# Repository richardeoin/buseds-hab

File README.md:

TODO: Find a better name for this project than "buseds-hab"!

### [Components List](Components.md)

### [Block Diagram](Block-Diagram.md)

### [Power Budget](power-budget.md)

### Design Notes

The electronics collects data from the sensors and GPS. [Common GPS errors](http://ukhas.org.uk/guides:common_coding_errors_payload_testing).

The data is formatted as a
[UKHAS Telemetry String](http://ukhas.org.uk/communication:protocol)
and transmitted on 434.075MHz using a NTX2
transmitter. [Useful guide to using NTX2](http://ukhas.org.uk/guides:linkingarduinotontx2).
The Telemetry Strings are also logged to a µSD card.

Gets received by Yaesu FT790R.

Audio links to laptop, UKHAS's
[dl-fldigi](http://ukhas.org.uk/projects:dl-fldigi) is used to decode and upload.

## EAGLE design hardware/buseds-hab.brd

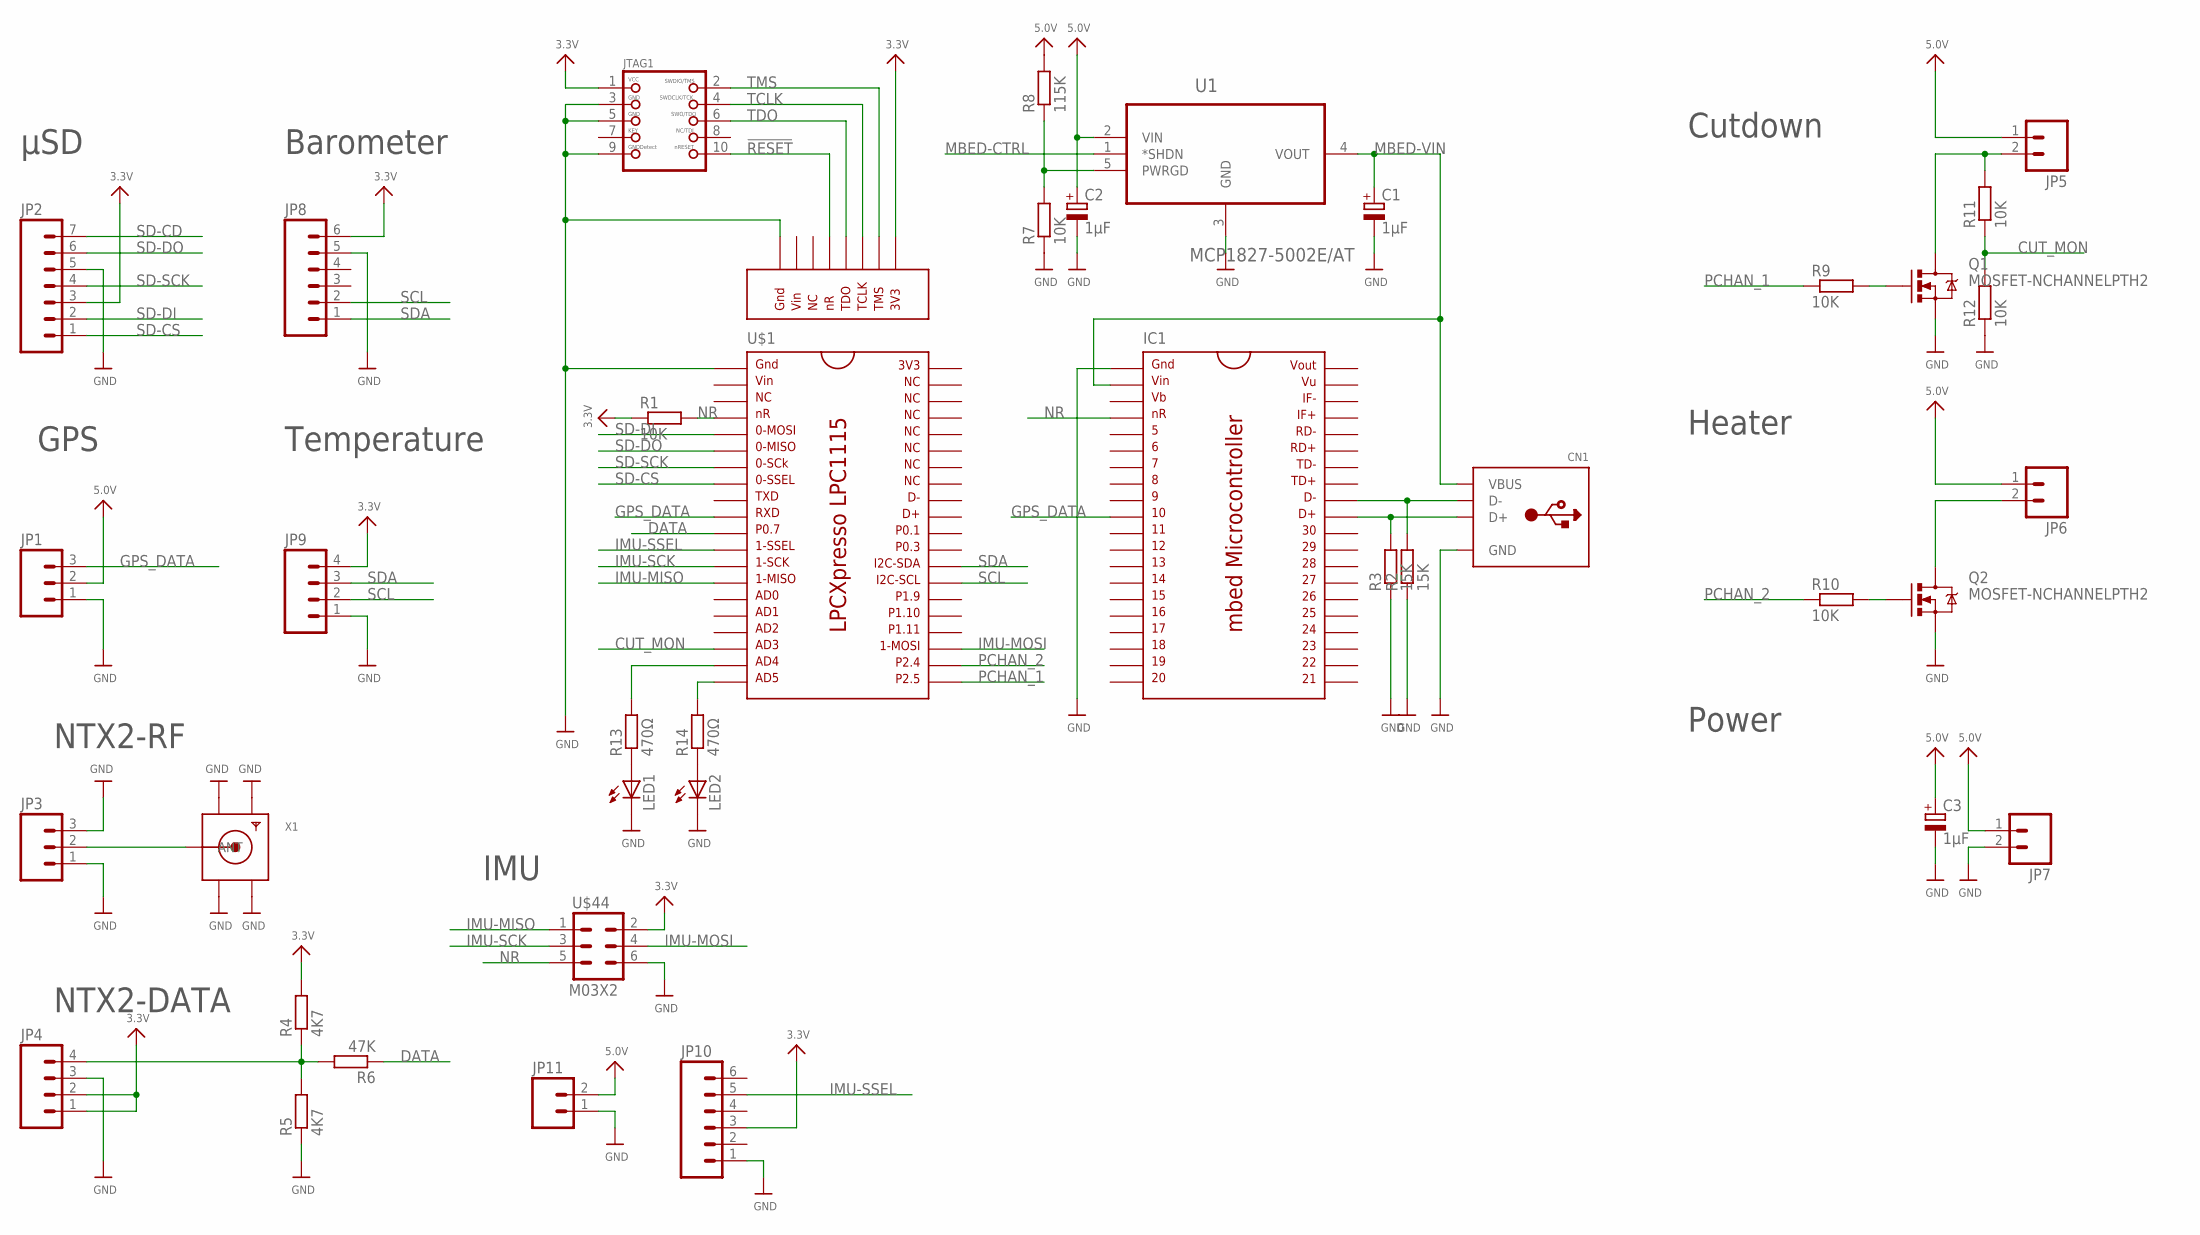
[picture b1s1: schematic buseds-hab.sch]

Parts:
C1, C2, C3: 1µF; E2-5
CN1: USB_TYPEAPTHFML; USB_HOST-PTH
IC1: MBED; DIL40_0.9
JP1, JP3: M03LOCK; 1X03_LOCK
JP2: M07LOCK; 1X07_LOCK
JP4, JP9: M04LOCK; 1X04_LOCK
JP5, JP6, JP7: M023.5MM_LOCK; SCREWTERMINAL-3.5MM-2_LOCK
JP8, JP10: M06LOCK; 1X06_LOCK
JP11: M02LOCK; 1X02_LOCK
JTAG1: JTAG-CORTEXM3; 2X05_1.27MM
LED1, LED2: LED3MM
Q1, Q2: MOSFET-NCHANNELPTH2; TO220V
R1, R7, R9, R10, R11, R12: 10K; 0204/7
R2, R3: 15K; 0204/7
R4, R5: 4K7; 0204/7
R6: 47K; 0204/7
R8: 115K; 0204/7
R13, R14: 470Ω; 0204/7
U1: MCP1827-5002E/AT; TO170P482X1024X3124-5P
U$1: LPCXPRESSOLPC; LPCXPRESSO
U$44: M03X2; 2X3_LOCK
X1: SMACONNECTOR; SMA90_DIP

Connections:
3.3V: JP2.3, JP4.1, JP4.2, JP8.6, JP9.4, JP10.3, JTAG1.1, R1.1, R4.2, U$1.P-1, U$44.2
5.0V: C2.+, C3.+, JP1.2, JP5.1, JP6.1, JP7.1, JP11.2, R8.2, U1.2 (VIN)
!RESET!: JTAG1.10, U$1.P-5
CUT_MON: R11.1, R12.2, U$1.18
D+: CN1.D+, IC1.31, R3.2
D-: CN1.D-, IC1.32, R2.2
DATA: R6.1, U$1.11
GND: C1.-, C2.-, C3.-, CN1.GND, IC1.1, JP1.1, JP2.5, JP3.1, JP3.3, JP4.3, JP7.2, JP8.5, JP9.1, JP10.1, JP11.1, JTAG1.3, JTAG1.5, JTAG1.9, LED1.K (C), LED2.K (C), Q1.3 (S), Q2.3 (S), R2.1, R3.1, R5.1, R7.1, R12.1, U1.3 (GND), U$1.1, U$1.P-8, U$44.6, X1.GND1, X1.GND2, X1.GND3, X1.GND4
GPS_DATA: IC1.10, JP1.3, U$1.10
IMU-MISO: U$1.14, U$44.1
IMU-MOSI: U$1.23, U$44.4
IMU-SCK: U$1.13, U$44.3
IMU-SSEL: JP10.5, U$1.12
MBED-CTRL: U1.1 (*SHDN)
MBED-VIN: C1.+, CN1.VBUS, IC1.2, U1.4 (VOUT)
unnamed: R7.2, R8.1, U1.5 (PWRGD)
unnamed: LED1.A, R13.1
unnamed: LED2.A, R14.1
unnamed: R14.2, U$1.20
unnamed: R13.2, U$1.19
NR: IC1.4, R1.2, U$1.4, U$44.5
PCHAN_1: R9.1, U$1.21
PCHAN_1_G: Q1.1 (G), R9.2
PCHAN_1_S: JP5.2, Q1.2 (D), R11.2
PCHAN_2: R10.1, U$1.22
PCHAN_2_G: Q2.1 (G), R10.2
PCHAN_2_S: JP6.2, Q2.2 (D)
RF: JP3.2, X1.ANTENNA (ANT)
RF-DATA: JP4.4, R4.1, R5.2, R6.2
SCL: JP8.2, JP9.2, U$1.27
SD-CD: JP2.7
SD-CS: JP2.1, U$1.8
SD-DI: JP2.2, U$1.5
SD-DO: JP2.6, U$1.6
SD-SCK: JP2.4, U$1.7
SDA: JP8.1, JP9.3, U$1.28
TCLK: JTAG1.4, U$1.P-3
TDO: JTAG1.6, U$1.P-4
TMS: JTAG1.2, U$1.P-2

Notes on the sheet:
µSD
GPS
NTX2-RF
NTX2-DATA
Temperature
Barometer
Cutdown
Heater
Power
IMU

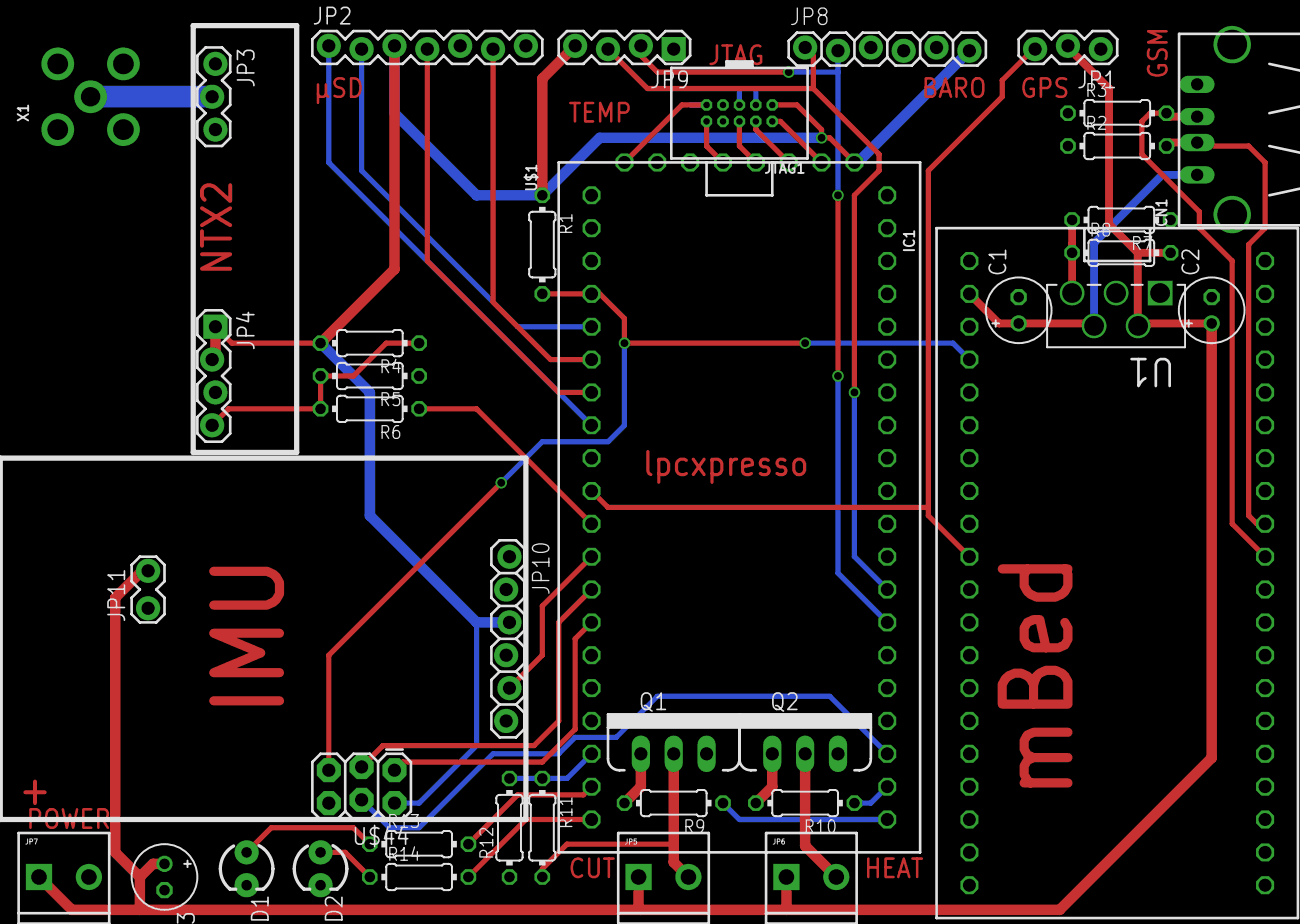
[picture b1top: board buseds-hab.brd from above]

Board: 2 copper layers, 39 parts (0 on the bottom side), 37 nets.

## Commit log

2013-11-15 Initial Commit of README
2013-11-15 Fixed up markdown syntax
2013-11-15 Another attempt at making the markdown look nice
2013-11-15 Split components list into Components.md
2013-11-15 Modified Components list to be a table
2013-11-15 Hopefully fixed table
2013-11-15 Added a couple more items to components table
2013-11-16 Added block diagram, design notes
2013-11-16 Added more design notes
2013-11-17 added more information for some components
    updated information on IMU and subcomponents + GPS + Radio
2013-11-17 Added correct part number and schematic link for IMU
2013-11-22 Block diagram file updated, but no actual changes made...
2013-11-22 Added to IMU component descriptions
2013-11-22 More component descriptions
2013-11-22 Added microcontrollers, SD card holder
2013-11-22 Added power budget
2013-11-22 Fixed table
2013-11-22 Added battery connector
2013-11-22 Created subtree for lpc source
2013-11-22 Adapted makefile for use with blackmagic debug probe on linux
2013-11-22 Added example unit test - square.c
2013-11-22 Added RTTY and associated test
2013-11-22 Added pin usage notes
2013-11-22 Got RTTY working
2013-11-22 Updated linker flags to include libc
2013-11-22 Updated lpc project name
2013-11-23 Fixed temperature sensor bus address
2013-11-23 Removed libc from linker flags, seems to cause hardfault. TODO: investiagte
2013-11-23 Added I2C libraries
2013-11-23 Added temperature sensor support
2013-11-23 Reformatted test output
2013-11-24 Removed binary, shouldn't have been commited anyhow!
2013-11-24 Added tests for TMP102
2013-11-24 Changed makefiles to allow compilation with lib math
2013-11-24 Added altitude calcuation function
2013-12-07 Added Field Test Log
2013-12-08 Tidied whitespace
2013-12-08 Implemented SPI slave for receiving IMU data
2013-12-08 Fixed description on SPI header
2013-12-08 Added code to process IMU data
2013-12-08 Added IMU firmware
2013-12-14 Added replacement pressure sensor
2013-12-14 Started minor parts list for things that will be soldered to the main PCB
2013-12-14 Initial revision of hardware
2013-12-14 Cropped board image
2013-12-14 Added JTAG connector
2013-12-15 Made space for voltage regulator tab
2014-01-04 Added resistors to minor components list
2014-01-04 Added connectors to minor components list
2014-01-09 Corrected JTAG1 connector to something more suitable
2014-01-27 Made basic updates for the new board
2014-01-28 Added header with LED macros
2014-01-28 Updated memory map for LPC1115
2014-01-28 Only use Green LED for the moment, Yellow LED overrides SWDIO
2014-01-30 Added code for barometer
2014-02-05 Basic implementation of communications protocol
2014-02-06 Updates to communication protocol from meeting 06/02/2014
2014-02-21 Whitespace things, accessor functions for imu, added test build for GPS code
2014-02-21 Added GPS parsing code and tests
2014-02-26 Added UKHAS protocol and tests
2014-02-26 Initial implementation of uart for the gps
2014-02-26 Initial implementation of SD card code
2014-02-26 Added macros for SD CS pin, fixed warnings
2014-02-28 Added headers for external controls
2014-03-14 Removed Pins.md, not needed & incorrect
2014-03-18 Added timeout on transactions to prevent an infinite wait
2014-03-18 Don't use the Yellow LED as it interferes with the programming interface
2014-03-18 Fixed control polarity for the mbed
2014-03-18 Fixed pins for cutdown and heat
2014-03-18 SD card code builds and runs, debugging still todo
2014-03-18 main.c updated for cutdown / heat and SD card
2014-03-21 Initial implementation of watchdog timer
2014-03-21 Rebuild sources.mk, fixed compiler errors on new sources
2014-03-21 SD card tested and working
2014-03-21 Clarified communications protocol
2014-03-21 New format for communication protocol page?
2014-03-21 Another format?
2014-03-21 New format done
2014-03-21 GPS string parsing working
2014-03-21 Implementation of UKHAS protocol now working
2014-03-21 Added buffering to rtty.c
2014-03-22 Ditched unused variable
2014-03-22 Added disk write interface which keeps track of the current block
2014-03-28 Implemented cutdown timer
2014-03-31 Modified protocol for cutdown timer
2014-03-31 Clarified decimal values in communication protocol
2014-03-31 Made "make test" actually work
2014-03-31 Added cutdown voltage to the protocol. TODO: Measurement code
2014-03-31 Use current time during protocol test, cutdown voltage to 1dp
2014-03-31 Stopped deactivating rtty between packets, apparently this mucks up dl-fldigi's auto-baud
2014-03-31 Added no lock detection
2014-03-31 Updates printing to only use formats available in nano.specs, reduceds resource load and hardfaults on processor
2014-03-31 Fixed float printing functions with working versions from UKHAS
2014-03-31 Fixed checksum issue
2014-03-31 Upper sideband it is...
2014-04-01 Tidied up main.c, added control logic for heater
2014-04-01 Fixed rounding edge case
2014-04-01 Added cutdown voltage monitoring
2014-04-04 Actually store the disk location properly
2014-04-04 Added extra data section for saving to the sd card
2014-04-05 Improved no lock handling (altitude is now zero'ed too)
2014-04-05 Extended watchdog timeout interval to 4 seconds
2014-04-05 Set interrupt priorities: 1st SysTick, 2nd Everything Else, 3rd Power Mon
2014-04-05 Altitude calcuation now works for the whole US standard atmosphere
2014-04-05 Tidy line endings
2014-04-05 Improve i2c timeouts
2014-04-05 Fixed WDT clocking
2014-04-05 Display sensible values when the barometer is disconnected
2014-04-05 Reduced SD card timeout
2014-04-05 Added preprocessor switch to enable watchdog
2014-04-05 Changes for testing
2014-04-05 Fixed sd read/write block size
2014-04-06 Cleared up confusion between geopotential and geometric altiudes. Data now matches with Wolfram Alpha pretty much perfectly.
2014-06-13 Set options for Flight on 14th/15th June 2014
2014-06-13 Verify checksums on GPS frames.
    Observed an error in the GPS frame reception (out of order characters) during testing.

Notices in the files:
parts and their libraries:
microbuilder_v3: This work is placed in the public domain, and may be freely used for commercial and non-commercial work with the following conditions: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
SparkFun: Licensing: CC v3.0 Share-Alike You are welcome to use this library for commercial purposes.
